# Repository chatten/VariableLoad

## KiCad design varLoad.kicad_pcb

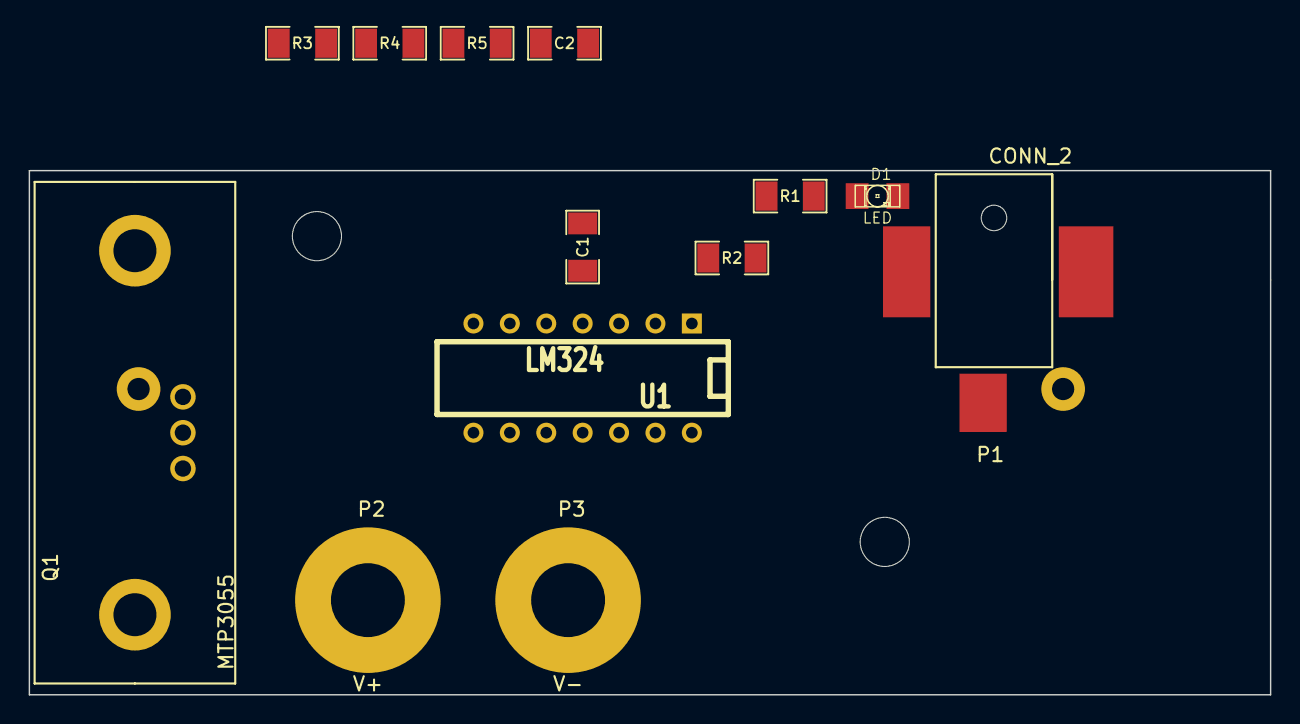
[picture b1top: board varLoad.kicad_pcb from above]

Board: 2 copper layers, 86.6 x 36.6 mm, 14 parts (1 on the bottom side), 7 nets, no tracks yet.

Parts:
C1: 0.1u; SM1206
C2: C; SM1206
D1: LED; LED-1206
P1: CONN_2; RASM722_PowerJack
P2: V+; bindingPost
P3: V-; bindingPost
Q1: MTP3055; TO220_W_HEATSINK
R1, R2, R3, R4, R5: 10k; SM1206
R6: 1; KAL50
U1: LM324; DIP-14__300

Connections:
+6V: C1.1, R1.2, R2.2, U1.4
GND: C1.2, C2.2, D1.2, P1.2, R4.1, R5.2, R6.2, U1.11
unnamed: D1.1, R1.1
unnamed: Q1.G, U1.7
unnamed: C2.1, Q1.S, R6.1, U1.6
unnamed: R3.1, U1.1, U1.2
unnamed: R3.2, R4.2, U1.5

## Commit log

2013-11-30 Initial Circuit from EEVBlog
2014-02-11 removed voltage divider and second op amp
2014-02-18 Started Associating Footprints. Re-Added second op amp
2014-03-07 created fet footprint
2014-03-08 created foorprint for 1ohm resistor
2014-03-10 started placement
